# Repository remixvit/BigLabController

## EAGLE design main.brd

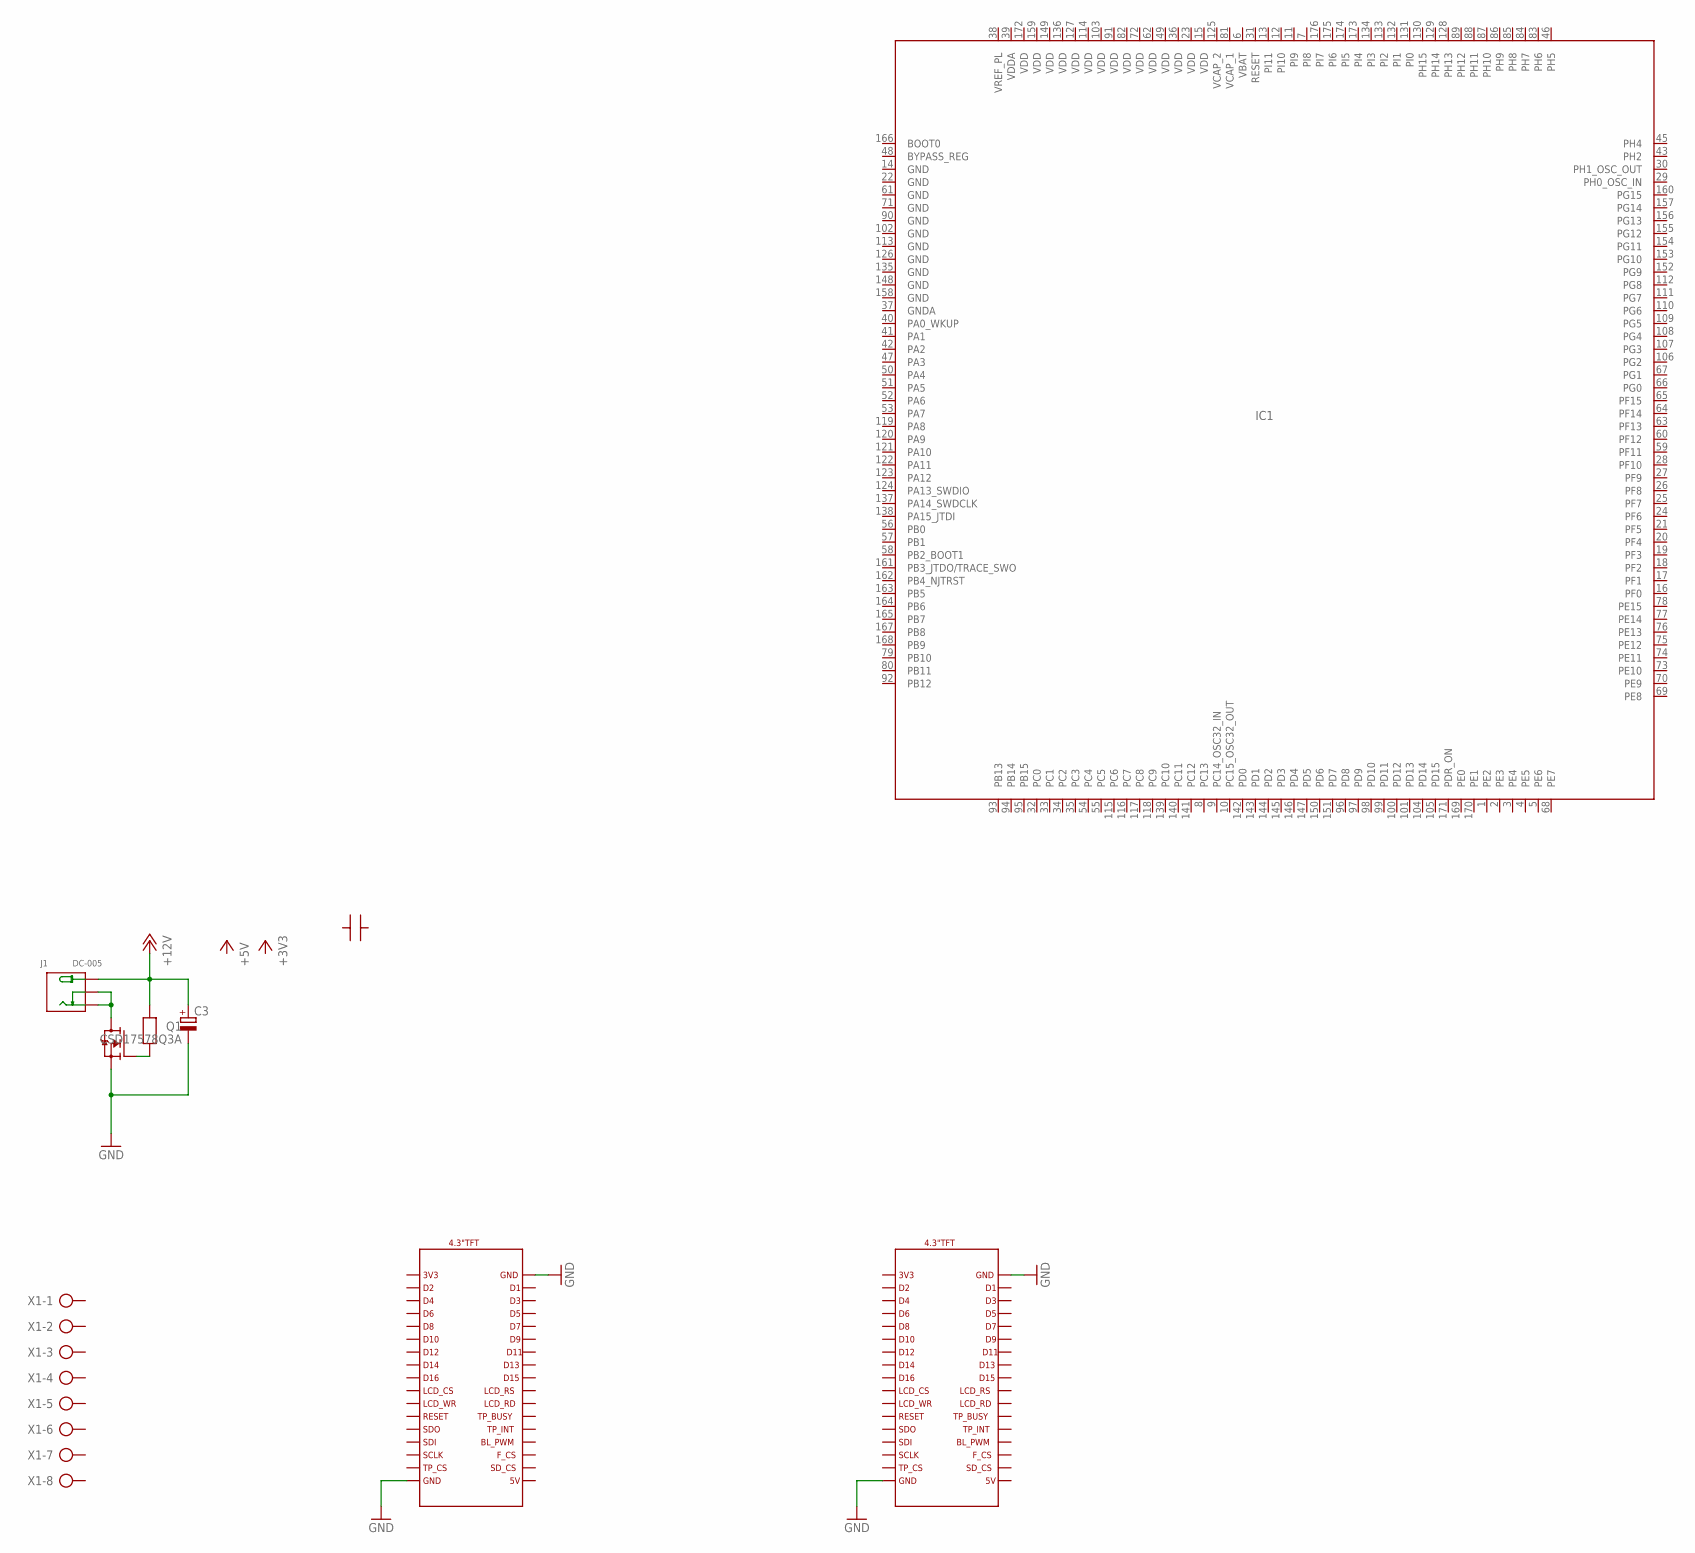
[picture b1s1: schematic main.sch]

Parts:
C1: CAP0603; C0603
C3: CPOL-EU153CLV-0807; 153CLV-0807
IC1: STM32F429IIT6; LQFP176
J1: DC-005; DCJ3P-14.2X11.0X9.0MM
Q1: CSD17578Q3A; VSONP8
R1: RES0603; R0603
U$1: 4.3"TFT; 4.3TFT
X1: AK500/8

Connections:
+12V: C3.+, J1.+, R1.1
GND: C3.-, IC1.14 (GND), IC1.22 (GND), IC1.61 (GND), IC1.71 (GND), IC1.90 (GND), IC1.102 (GND), IC1.113 (GND), IC1.126 (GND), IC1.135 (GND), IC1.148 (GND), IC1.158 (GND), Q1.S1 (S), Q1.S2 (S), Q1.S3 (S), U$1.JP1_1, U$1.JP1_34, U$1.JP2_1, U$1.JP2_34
GNDA: IC1.37 (GNDA)
unnamed: Q1.G, R1.2
unnamed: J1.-1 (-), J1.-2 (CDN), Q1.D1 (D), Q1.D2 (D), Q1.D3 (D), Q1.D4 (D), Q1.D5 (D)
PDR_ON: IC1.171 (PDR_ON)
VBAT: IC1.6 (VBAT)
VCAP_1: IC1.81 (VCAP_1)
VCAP_2: IC1.125 (VCAP_2)
VDD: IC1.15 (VDD), IC1.23 (VDD), IC1.36 (VDD), IC1.49 (VDD), IC1.62 (VDD), IC1.72 (VDD), IC1.82 (VDD), IC1.91 (VDD), IC1.103 (VDD), IC1.114 (VDD), IC1.127 (VDD), IC1.136 (VDD), IC1.149 (VDD), IC1.159 (VDD), IC1.172 (VDD)
VDDA: IC1.39 (VDDA)
VREF_PL: IC1.38 (VREF_PL)

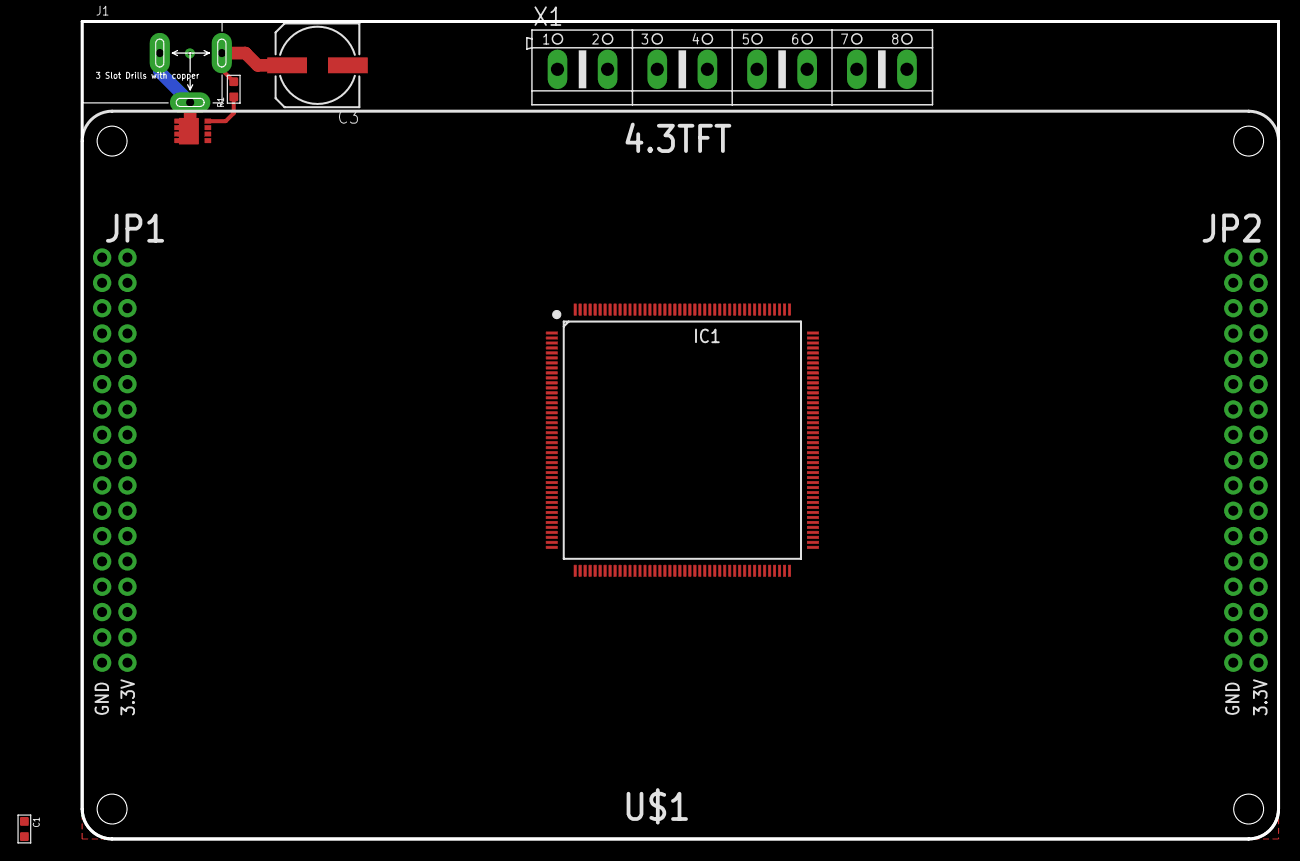
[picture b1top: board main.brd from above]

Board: 2 copper layers, 120.0 x 82.0 mm, 8 parts (0 on the bottom side), 5 nets.

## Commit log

2015-12-01 Create Board and Shematic
2015-12-01 BugFix
2015-12-14 Add USB Pheripheral Board
2015-12-15 Add Amplifer Board
